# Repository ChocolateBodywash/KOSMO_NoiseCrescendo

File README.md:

## KOSMO Format Noise Crescendo

This is a compact module designed to produce noise crescendos for transitions, sweeps, and other crazy sounds. It’s built around a simple transistor noise circuit feeding into a low-pass filter.
The filter itself is adapted from Look Mum No Computer’s Synth Voice on a Breadboard video:

I adjusted a few component values to adjust the resonance and CV behaviour.

### Can it just be used as a filter?
Yes. With a passive summing mixer, an input jack, and an on/off switch for the noise, this becomes a straightforward low-pass filter.
LM13700s cost $4 USD on Tayda. In Canadian terms, that’s… let’s just say ‘not cheap,’ so I prefer modules that pull double duty.

---

Note: This was created by a hobbyist with no formal engineering training outside various late night YouTube binges. 
I’ve confirmed these designs to work but I make no guarantees on the design working efficiently.. or working at all.

Credit: Analog Output (Richard Holmes) for footprint libraries and front panel templates.

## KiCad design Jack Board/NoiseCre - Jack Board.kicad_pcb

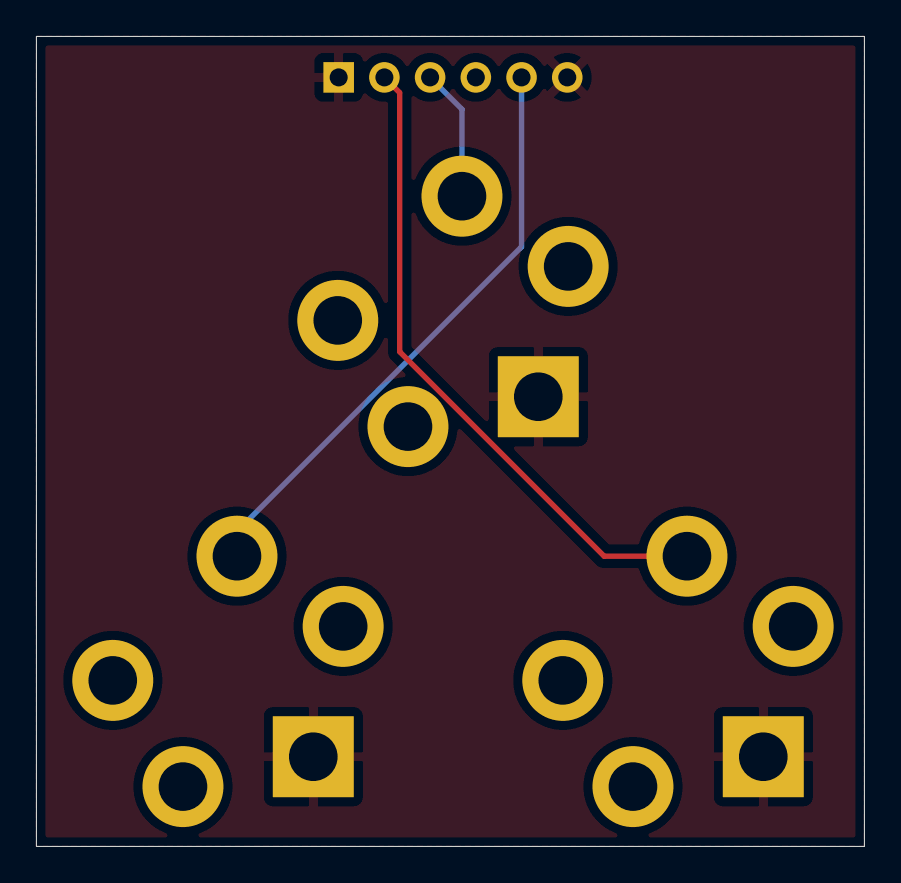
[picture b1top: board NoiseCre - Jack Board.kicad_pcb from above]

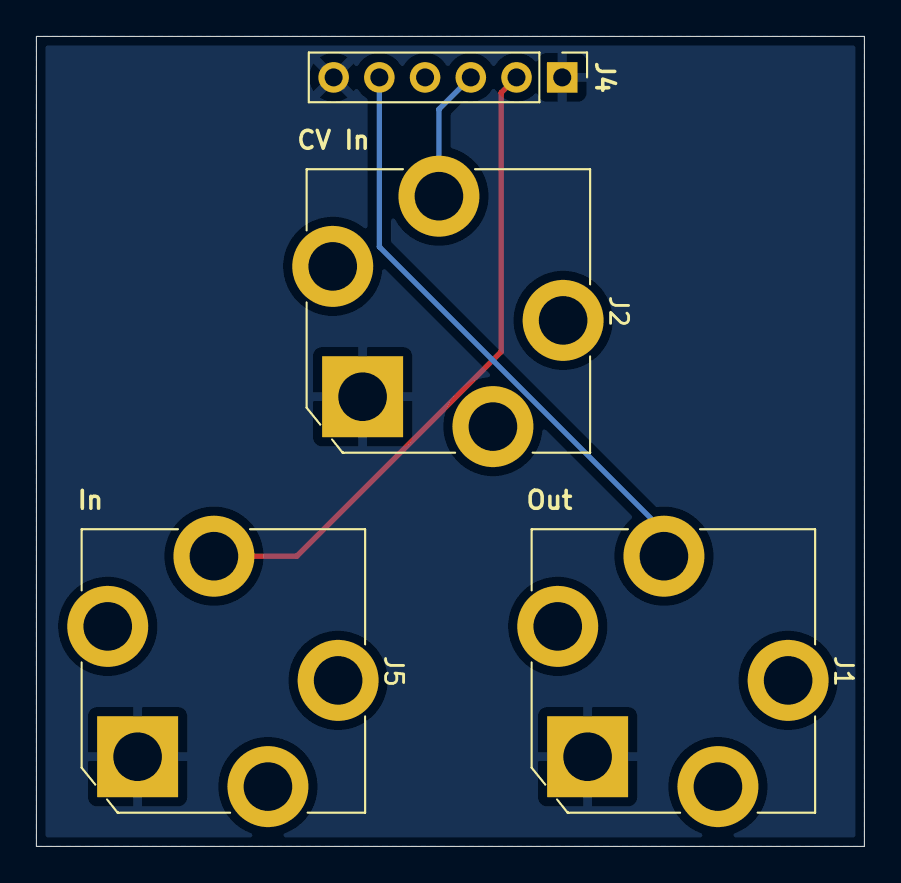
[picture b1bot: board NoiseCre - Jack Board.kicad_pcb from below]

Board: 2 copper layers, 46.0 x 45.0 mm, 4 parts (4 on the bottom side), 4 nets.

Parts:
J1: Out; Jack_6.35mm_PJ_629HAN
J2: CV In; Jack_6.35mm_PJ_629HAN
J4: Conn_01x06; PinHeader_1x06_P2.54mm_Vertical
J5: In; Jack_6.35mm_PJ_629HAN

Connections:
GND: J1.S, J2.S, J4.1, J4.6, J5.S
unnamed: J4.2, J5.T
unnamed: J2.T, J4.3
unnamed: J1.T, J4.5

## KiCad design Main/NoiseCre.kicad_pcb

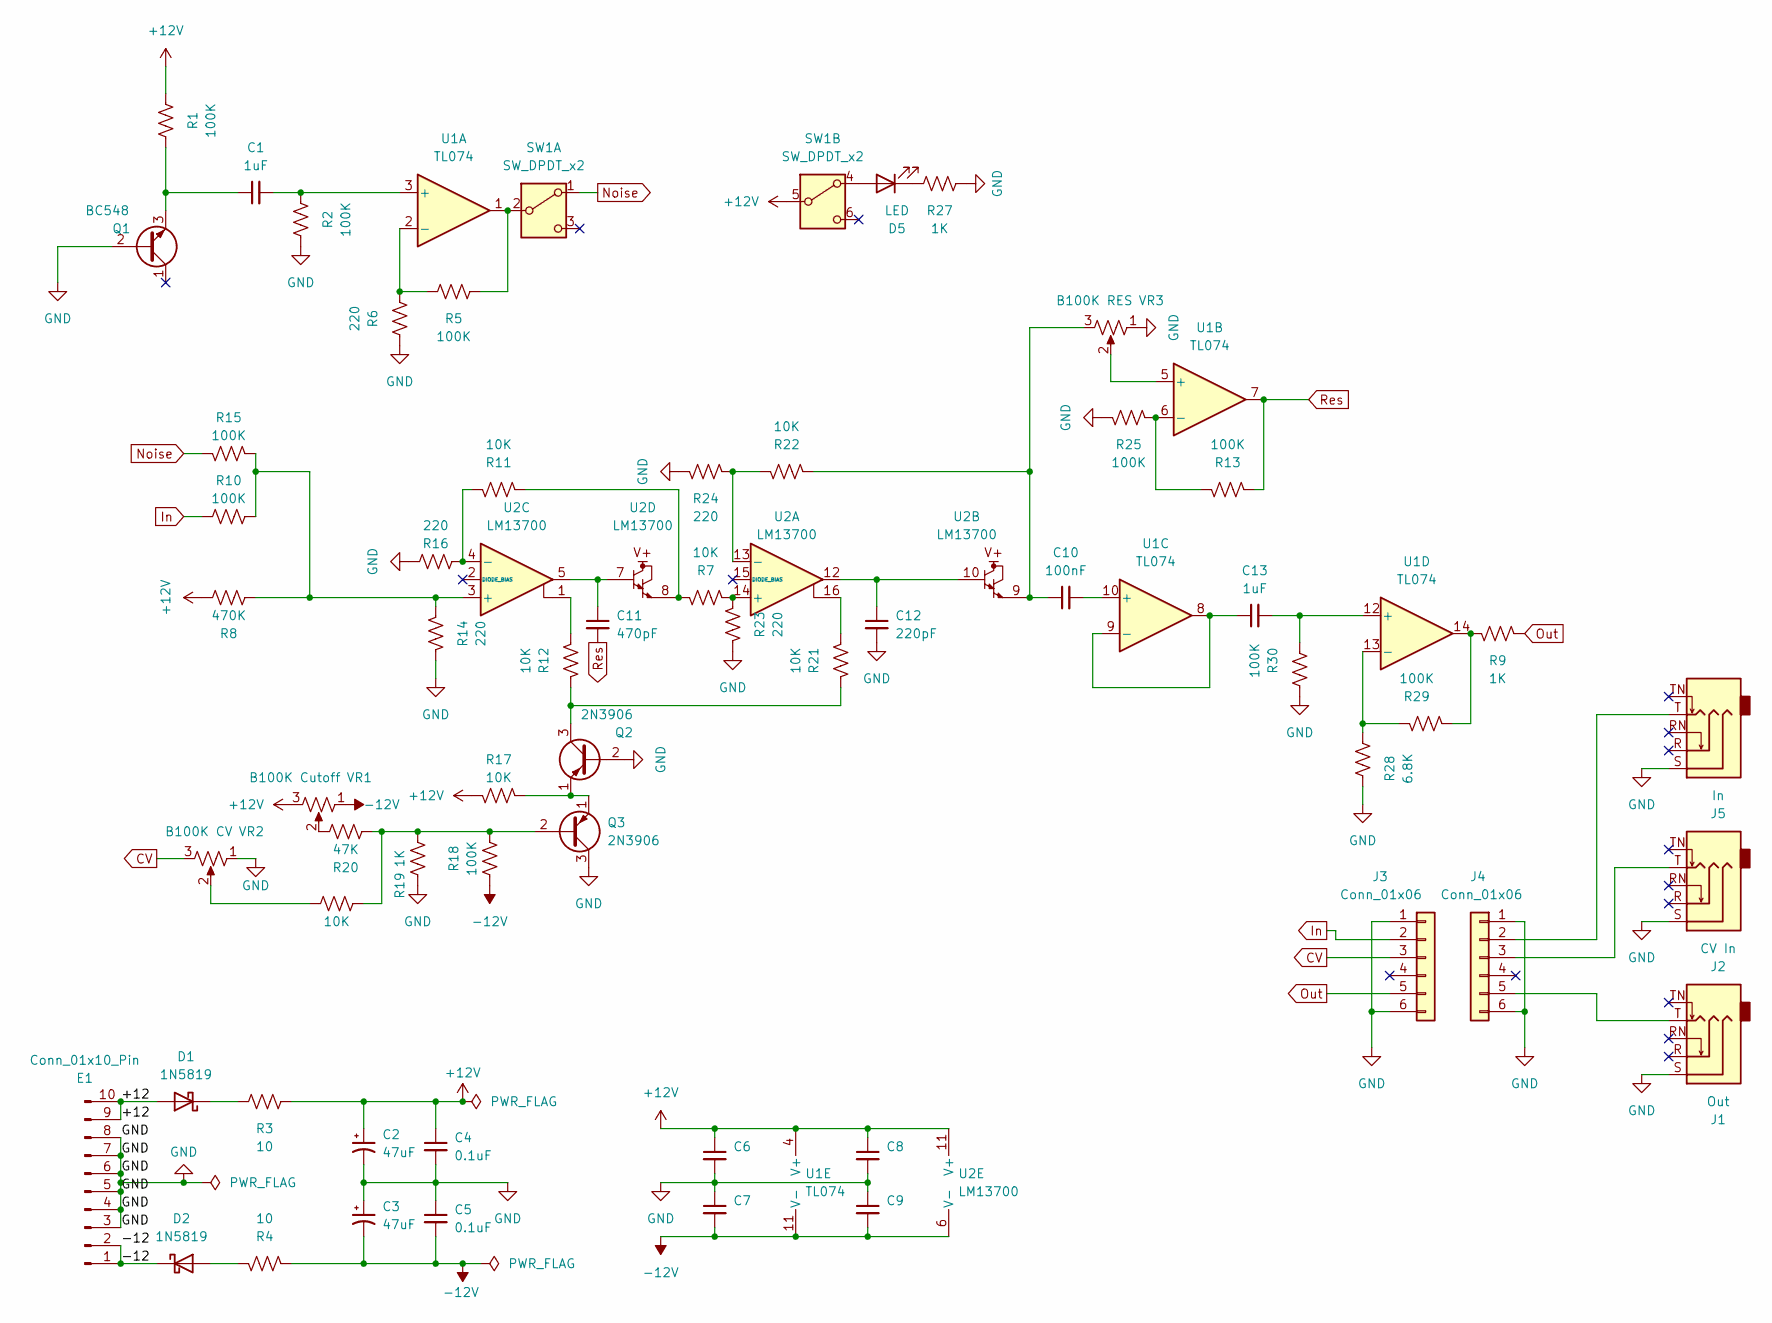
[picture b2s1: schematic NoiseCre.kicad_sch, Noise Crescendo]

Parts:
C1, C13: 1uF; C_Rect_L7.2mm_W5.5mm_P5.00mm_FKS2_FKP2_MKS2_MKP2
C2, C3: 47uF; CP_Radial_D5.0mm_P2.50mm
C4, C5, C6, C7, C8, C9: 0.1uF; C_Disc_D3.0mm_W1.6mm_P2.50mm
C10: 100nF; C_Rect_L7.2mm_W2.5mm_P5.00mm_FKS2_FKP2_MKS2_MKP2
C11: 470pF; C_Disc_D3.0mm_W1.6mm_P2.50mm
C12: 220pF; C_Disc_D3.0mm_W1.6mm_P2.50mm
D1, D2: 1N5819; D_DO-41_SOD81_P10.16mm_Horizontal
D5: LED; LED_D5.0mm
E1: Conn_01x10_Pin; Pins_2x05_2.54mm_TH_EurorackPower_Shrouded
J1: Out; Jack_6.35mm_PJ_629HAN
J2: CV In; Jack_6.35mm_PJ_629HAN
J3, J4: Conn_01x06; PinHeader_1x06_P2.54mm_Vertical
J5: In; Jack_6.35mm_PJ_629HAN
Q1: BC548; TO-92_Inline_Wide
Q2, Q3: 2N3906; TO-92_Inline_Wide
R1, R2, R5, R10, R13, R15, R18, R25, R29, R30: 100K; R_Axial_DIN0207_L6.3mm_D2.5mm_P10.16mm_Horizontal
R3, R4: 10; R_Axial_DIN0207_L6.3mm_D2.5mm_P10.16mm_Horizontal
R6, R14, R16, R23, R24: 220; R_Axial_DIN0207_L6.3mm_D2.5mm_P10.16mm_Horizontal
R7, R11, R12, R17, R21, R22, R26: 10K; R_Axial_DIN0207_L6.3mm_D2.5mm_P10.16mm_Horizontal
R8: 470K; R_Axial_DIN0207_L6.3mm_D2.5mm_P10.16mm_Horizontal
R9, R19, R27: 1K; R_Axial_DIN0207_L6.3mm_D2.5mm_P10.16mm_Horizontal
R20: 47K; R_Axial_DIN0207_L6.3mm_D2.5mm_P10.16mm_Horizontal
R28: 6.8K; R_Axial_DIN0207_L6.3mm_D2.5mm_P10.16mm_Horizontal
SW1: SW_DPDT_x2; DPDT-toggle-switch-1M-seriesx
U1: TL074; DIP-14_W7.62mm_Socket_LongPads
U2: LM13700; DIP-16_W7.62mm_Socket_LongPads
VR1: B100K Cutoff; Potentiometer_Alpha_RD901F-40-00D_Single_Vertical
VR2: B100K CV; Potentiometer_Alpha_RD901F-40-00D_Single_Vertical
VR3: B100K RES; Potentiometer_Alpha_RD901F-40-00D_Single_Vertical

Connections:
+12V: C2.1, C4.1, C6.1, C8.1, R1.2, R3.2, R8.2, R17.2, SW1.5 (B), U1.4 (V+), U2.11 (V+), VR1.3
-12V: C3.2, C5.2, C7.2, C9.2, R4.2, R18.1, U1.11 (V-), U2.6 (V-), VR1.1
/+12: D1.2 (A), E1.9, E1.10
/-12: D2.1 (K), E1.1, E1.2
CV: J3.3, VR2.3
GND: C2.2, C3.1, C4.2, C5.1, C6.2, C7.1, C8.2, C9.1, C12.2, E1.3, E1.4, E1.5, E1.6, E1.7, E1.8, J1.S, J2.S, J3.1, J3.6, J4.1, J4.6, J5.S, Q1.2 (B), Q2.2 (B), Q3.3 (C), R2.1, R6.2, R14.2, R16.2, R19.1, R23.2, R24.2, R25.2, R27.2, R28.1, R30.2, VR2.1, VR3.1
In: J3.2, R10.1
unnamed: C10.1, R22.2, U2.9, VR3.3
unnamed: C11.1, U2.5, U2.7
unnamed: C12.1, U2.10, U2.12
unnamed: D1.1 (K), R3.1
unnamed: D2.2 (A), R4.1
unnamed: D5.2 (A), SW1.4 (A)
unnamed: D5.1 (K), R27.1
unnamed: J1.T, J4.5
unnamed: J2.T, J4.3
unnamed: J4.2, J5.T
unnamed: C1.1, Q1.3 (E), R1.1
unnamed: Q2.3 (C), R12.1, R21.1
unnamed: Q2.1 (E), Q3.1 (E), R17.1
unnamed: Q3.2 (B), R18.2, R19.2, R20.1, R26.1
unnamed: R7.1, R11.2, U2.8
unnamed: R12.2, U2.1
unnamed: R20.2, VR1.2
unnamed: R21.2, U2.16
unnamed: R26.2, VR2.2
unnamed: R9.2, R29.2, U1.14
unnamed: R5.2, SW1.2 (B), U1.1
unnamed: C1.2, R2.2, U1.3 (+)
unnamed: R5.1, R6.1, U1.2 (-)
unnamed: U1.5 (+), VR3.2
unnamed: R13.1, R25.1, U1.6 (-)
unnamed: C10.2, U1.10 (+)
unnamed: C13.1, U1.8, U1.9 (-)
unnamed: C13.2, R30.1, U1.12 (+)
unnamed: R28.2, R29.1, U1.13 (-)
unnamed: R7.2, R23.1, U2.14 (+)
unnamed: R22.1, R24.1, U2.13 (-)
unnamed: R8.1, R10.2, R14.1, R15.1, U2.3 (+)
unnamed: R11.1, R16.1, U2.4 (-)
Noise: R15.2, SW1.1 (A)
Out: J3.5, R9.1
Res: C11.2, R13.2, U1.7

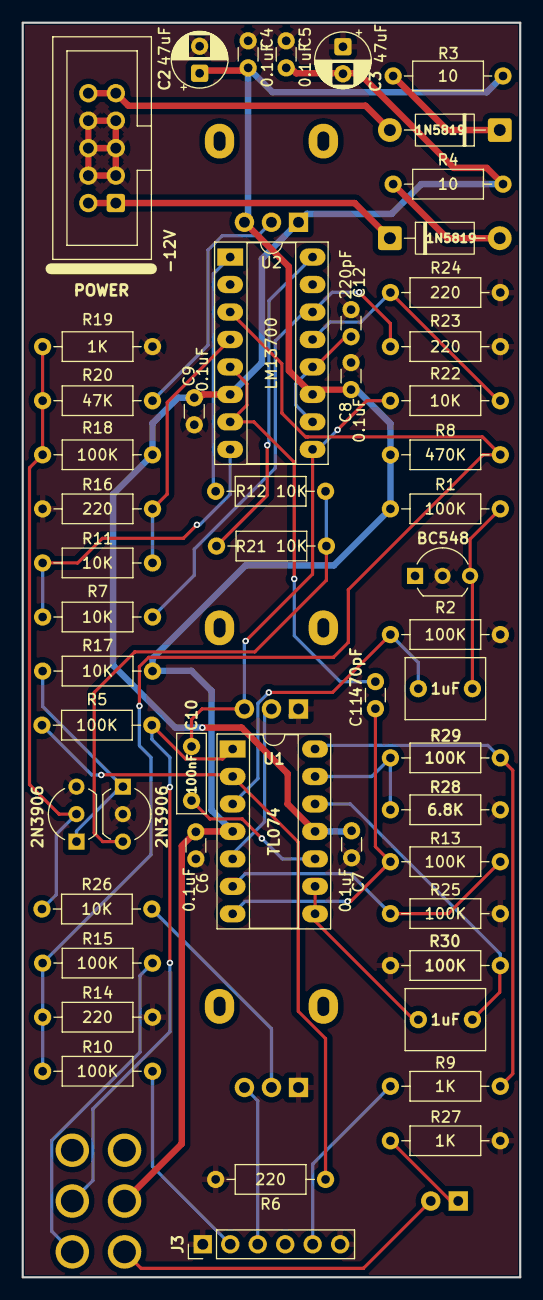
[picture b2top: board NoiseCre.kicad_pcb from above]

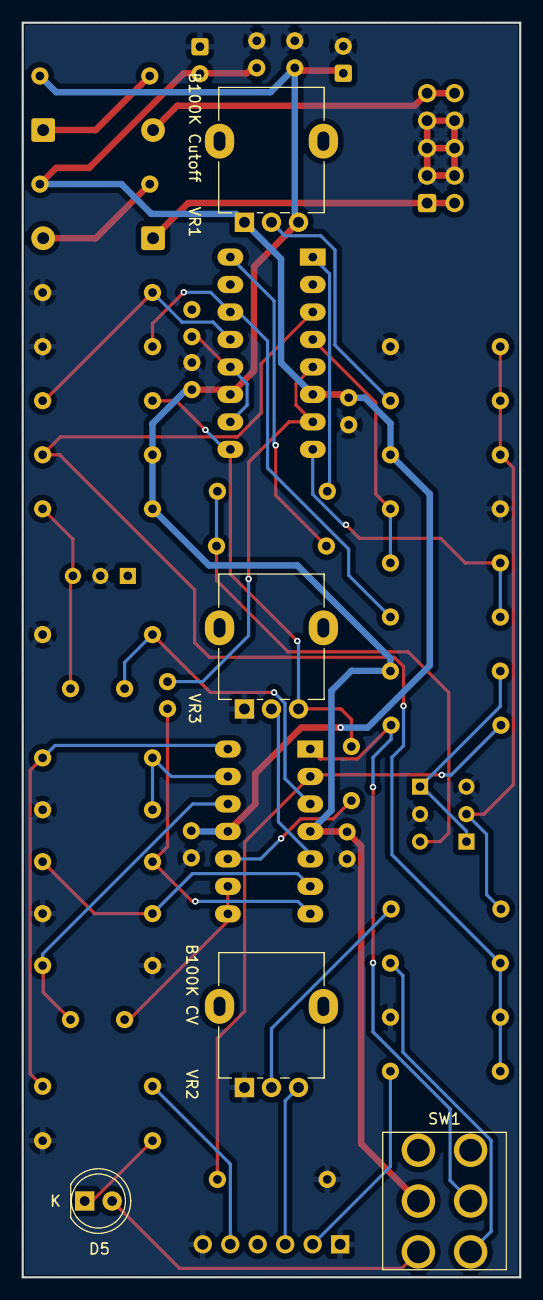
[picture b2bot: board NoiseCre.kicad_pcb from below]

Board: 2 copper layers, 46.0 x 116.0 mm, 57 parts (5 on the bottom side), 40 nets.

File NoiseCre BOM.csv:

Reference,Value,Datasheet,Package,Qty,
C1,1uF,~,Box Style Film Capacitor,1,
"C2,C3",47uF,~,Electrolytic Capacitor,2,
"C4,C5,C6,C7,C8,C9",0.1uF,~,Ceramic Disc Capacitor,6,
C10,100nF,~,Box Style Film Capacitor,1,
C11,470pF,~,Ceramic Disc Capacitor,1,
C12,220pF,~,Ceramic Disc Capacitor,1,
"D1,D2",1N5819,http://www.vishay.com/docs/88525/1n5817.pdf,Diode_THT:D_DO-41_SOD81_P10.16mm_Horizontal,2,
D5,LED,~,LED 5.0mm,1,
E1,Conn_01x10_Pin,~,Pins_2x05_2.54mm_TH_EurorackPower_Shrouded,1,
J1,Out,~,Jack_6.35mm,1,
J2,CV In,~,Jack_6.35mm,1,
"J3,J4",Conn_01x06,~,Connector_PinHeader_2.54mm:PinHeader_1x06_P2.54mm_Vertical,2,
J5,In,~,Jack_6.35mm,1,
Q1,BC548,https://www.onsemi.com/pub/Collateral/BC550-D.pdf,THT:TO-92_Inline_Wide,1,
"Q2,Q3",2N3906,https://www.onsemi.com/pub/Collateral/2N3906-D.PDF,THT:TO-92_Inline_Wide,2,
"R1,R2,R5,R10,R13,R15,R18,R25",100K,~,Metal Film 1/4 Resistor,8,
"R3,R4",10,~,Metal Film 1/4 Resistor,2,
"R6,R14,R16,R23,R24",220,~,Metal Film 1/4 Resistor,5,
"R7,R11,R12,R17,R21,R22,R26",10K,~,Metal Film 1/4 Resistor,7,
R8,470K,~,Metal Film 1/4 Resistor,1,
"R9,R19,R27",1K,~,Metal Film 1/4 Resistor,3,
R20,47K,~,Metal Film 1/4 Resistor,1,
SW1,SW_DPDT_x2,~,DPDT switch,1,
U1,TL072,http://www.ti.com/lit/ds/symlink/tl071.pdf,DIP-8_W7.62mm,1,
U2,LM13700,http://www.ti.com/lit/ds/symlink/lm13700.pdf,DIP-16_W7.62mm,1,
VR1,B100K Cutoff,~,Potentiometer_Alpha_RD901F-40-00D_Single_Vertical,1,
VR2,B100K CV,~,Potentiometer_Alpha_RD901F-40-00D_Single_Vertical,1,
VR3,B100K RES,~,Potentiometer_Alpha_RD901F-40-00D_Single_Vertical,1,

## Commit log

2025-10-05 Upload
2025-10-05 Panel change
2025-10-29 Upload Schematics
2025-11-20 Updated gain output
2026-05-28 Gerbers Added
